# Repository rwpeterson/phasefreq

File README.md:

# phasefreq
 Phase-frequency detector PCB built around the AD9901

## Design goals

* Simple, connectorized element to replace an analog mixer in rf test setups
* Requires only dc power to operate (no programming)
* 10 MHz, ideally 100 MHz bandwidth (10 MHz is reasonable without impedance control in fabrication)
* Accommodate analog input (Analog ADCMP564 comparator, with settable threshold and hysteresis)
* Perform PFD calculation (Analog AD9901 phase-frequency discriminator, ECL logic family)
* Low-pass filter to convert PFD output's pulse train duty cycle to a dc voltage
* Tunable output offset, jumper-switchable sign of gain
* This is basically a subset of the reference design in Fig. 12 of the [AD9901 datasheet](https://www.analog.com/media/en/technical-documentation/data-sheets/AD9901.pdf), which describes a complete PLL circuit with discrete comparator, PFD, VCO, divider, etc. Here we wish to implement only the comparator, phase-frequency detector, and loop filter

## What is a PFD?

A phase-frequency detector (or phase-frequency discriminator) is similar to an analog mixer, in that if the LO and RF frequencies are the same, its output is proportional to the relative phase between them. However, if the LO and RF frequencies differ, a PFD will output a constant voltage whose sign indicates which of the two frequencies is larger. In this case, an analog mixer would produce IF beatnotes at the sum and difference frequencies. This second characteristic of a PFD is useful to more quickly bring a feedback system such as a PLL into lock.

## Other options?

Of course, an analog mixer may be perfectly suitable for your application. More sophisticated PLL ICs contain builtin PFDs as part of the feedback loop. Some evaluation boards expose enough functionality to use them solely as a PFD, but they are prohibitively expensive for many applications where a simple PFD would be beneficial, and often need to be programmed or initialized at the point of use.

## Characterization

### Figure 1: Bidirectional phase sweep (RF and LO at 10 MHz)
Scanning the relative phase of the inputs demonstrates the linear phase detection and capture range. The location of the linear phase detection is modulo 2 pi as expected. However, when the phase is scanned away from a given phase detection range, the IF output will rail for one additional phase cycle before phase-slipping to the *second* capture range 4 pi away (as shown). For frequencies > 50 MHz, the ends of the phase detection range will be distorted (see AD9901 datasheet, Fig. 7).

### Figure 2: Frequency discrimination characteristic, LO = 10 MHz
When the RF and LO frequencies differ substantially, the PFD outputs a constant voltage indicating which is higher.

## Prototype

### Figure 3: revB1 prototype in 3D-printed case (lid removed)
This is the device used for the above characterization plots.

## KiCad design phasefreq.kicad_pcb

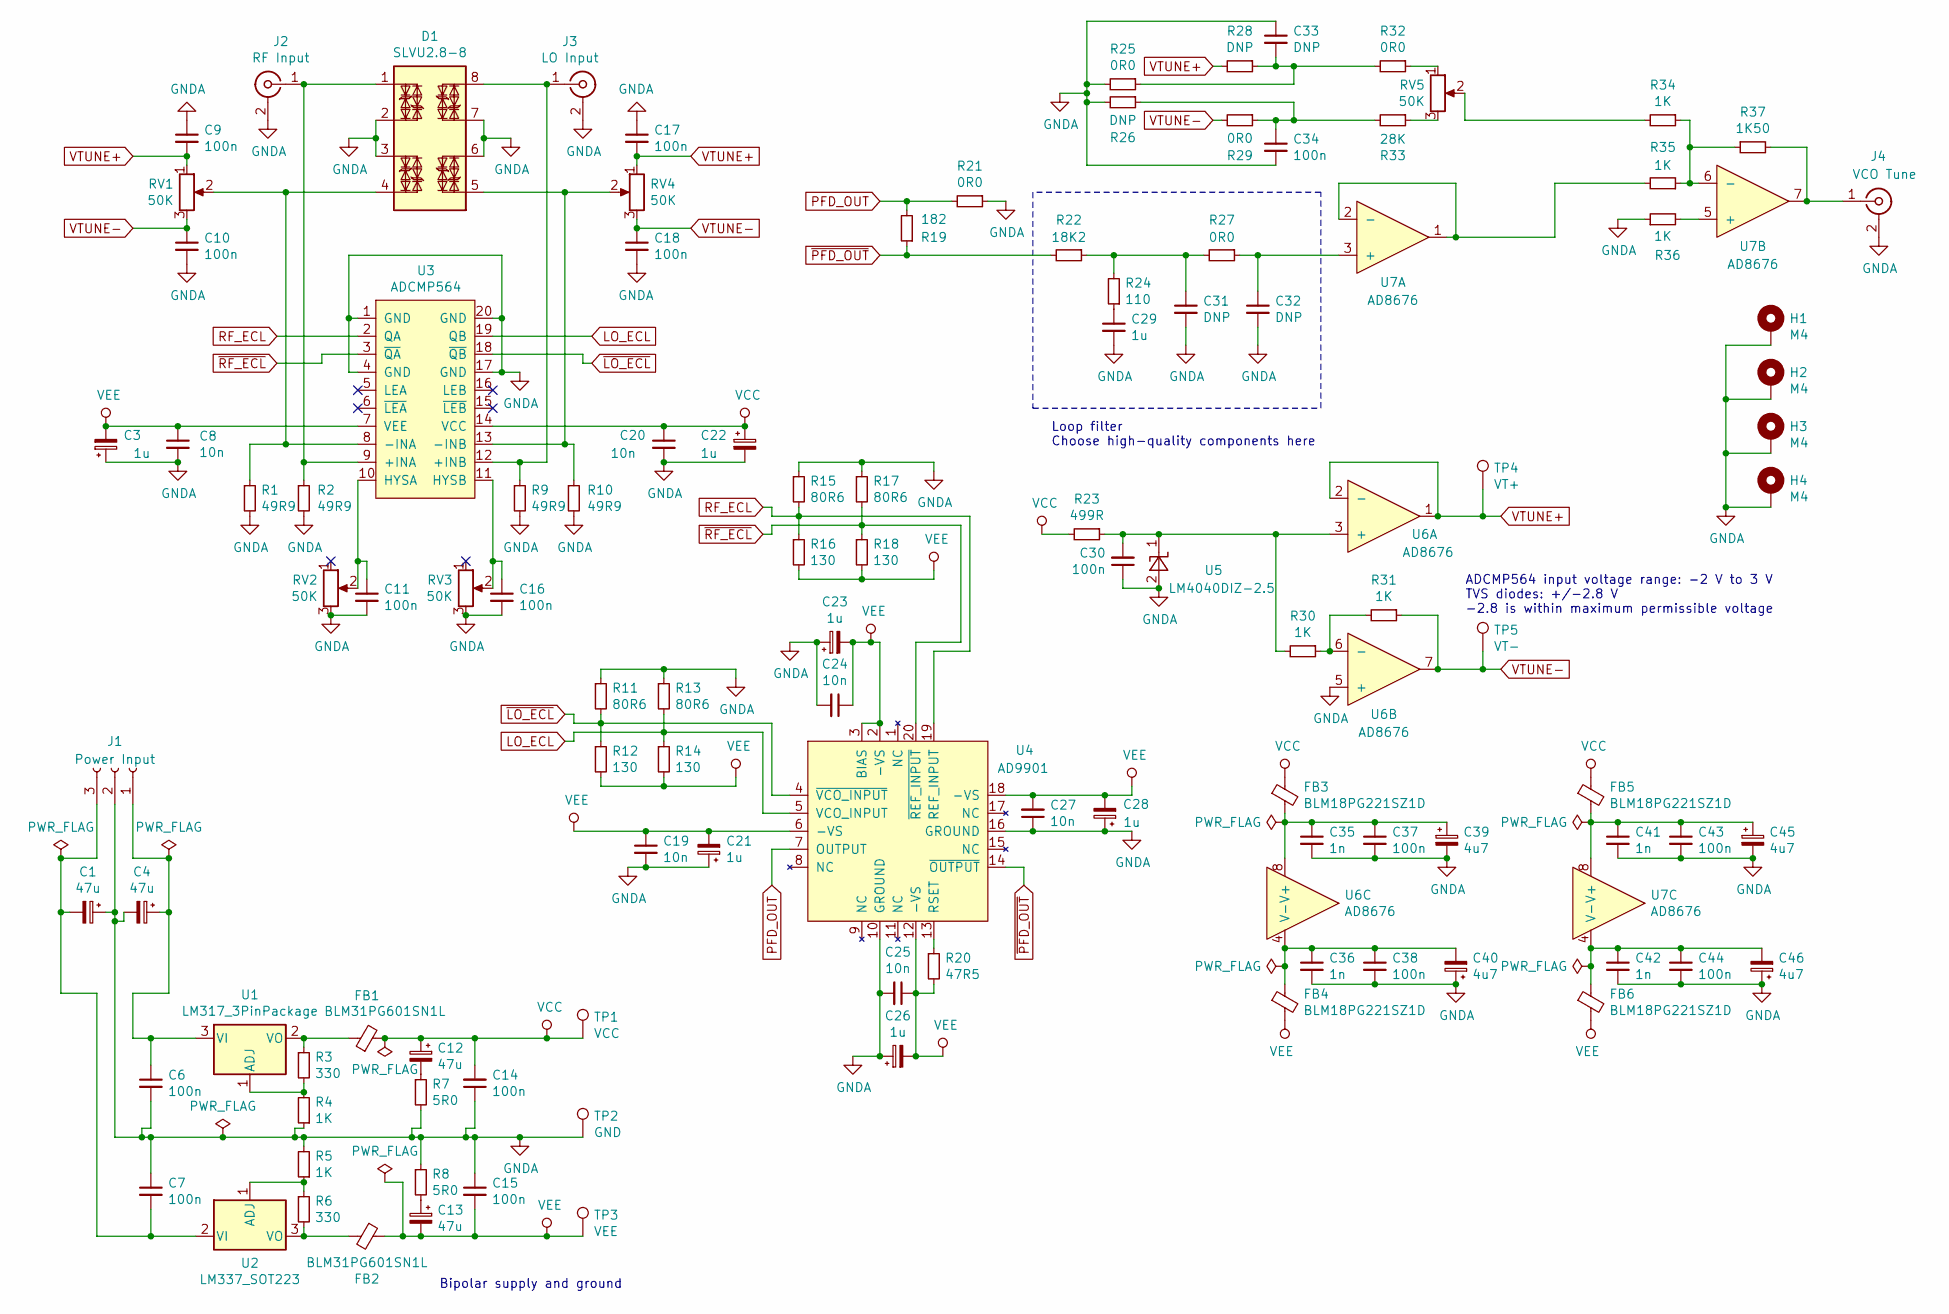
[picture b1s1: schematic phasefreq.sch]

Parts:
C1, C4: 47u; CP_EIA-7343-43_Kemet-X
C3, C21, C22, C23, C26, C28: 1u; CP_EIA-1608-10_AVX-L
C6, C7, C9, C10, C11, C14, C15, C16, C17, C18, C30, C34, C37, C38, C43, C44: 100n; C_0603_1608Metric
C8, C19, C20, C24, C25, C27: 10n; C_0603_1608Metric
C12, C13: 47u; CP_EIA-3216-18_Kemet-A
C29: 1u; C_0603_1608Metric
C31, C32, C33: DNP; C_0603_1608Metric
C35, C36, C41, C42: 1n; C_0603_1608Metric
C39, C40, C45, C46: 4u7; CP_EIA-1608-10_AVX-L
D1: SLVU2.8-8; SOIC-8_3.9x4.9mm_P1.27mm
FB1, FB2: BLM31PG601SN1L; L_1206_3216Metric
FB3, FB4, FB5, FB6: BLM18PG221SZ1D; L_0603_1608Metric
H1, H2, H3, H4: M4; MountingHole_4.3mm_M4_Pad_Via
J1: Power Input; JST_XH_B3B-XH-A_1x03_P2.50mm_Vertical
J2: RF Input; SMA_Amphenol_132289_EdgeMount
J3: LO Input; SMA_Amphenol_132289_EdgeMount
J4: VCO Tune; SMA_Amphenol_132289_EdgeMount
R1, R2, R9, R10: 49R9; R_0603_1608Metric
R3, R6: 330; R_0603_1608Metric
R4, R5, R30, R31, R34, R35, R36: 1K; R_0603_1608Metric
R7, R8: 5R0; R_0603_1608Metric
R11, R13, R15, R17: 80R6; R_0603_1608Metric
R12, R14, R16, R18: 130; R_0603_1608Metric
R19: 182; R_0603_1608Metric
R20: 47R5; R_0603_1608Metric
R21, R25, R27, R29, R32: 0R0; R_0603_1608Metric
R22: 18K2; R_0603_1608Metric
R23: 499R; R_0603_1608Metric
R24: 110; R_0603_1608Metric
R26, R28: DNP; R_0603_1608Metric
R33: 28K; R_0603_1608Metric
R37: 1K50; R_0603_1608Metric
RV1, RV2, RV3, RV4, RV5: 50K; Potentiometer_Vishay_TS53YJ_Vertical
TP1: VCC; TestPoint_THTPad_D1.5mm_Drill0.7mm
TP2: GND; TestPoint_THTPad_D1.5mm_Drill0.7mm
TP3: VEE; TestPoint_THTPad_D1.5mm_Drill0.7mm
TP4: VT+; TestPoint_THTPad_D1.5mm_Drill0.7mm
TP5: VT-; TestPoint_THTPad_D1.5mm_Drill0.7mm
U1: LM317_3PinPackage; SOT-223-3_TabPin2
U2: LM337_SOT223; SOT-223-3_TabPin2
U3: ADCMP564; QSOP-20_3.9x8.7mm_P0.635mm
U4: AD9901; PLCC-20
U5: LM4040DIZ-2.5; SOT-23
U6, U7: AD8676; SOIC-8_3.9x4.9mm_P1.27mm

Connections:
GNDA: C1.1, C3.1, C4.2, C6.2, C7.1, C8.2, C9.1, C10.2, C11.2, C14.1, C15.1, C16.2, C17.1, C18.2, C19.2, C20.2, C21.1, C22.2, C23.1, C24.2, C25.2, C26.1, C27.1, C28.1, C29.2, C30.1, C31.2, C32.2, C33.1, C34.2, C35.2, C36.2, C37.2, C38.2, C39.2, C40.1, C41.2, C42.2, C43.2, C44.2, C45.2, C46.1, D1.2 (TVS2), D1.3 (TVS1), D1.6 (TVS2), D1.7 (TVS1), H1.1, H2.1, H3.1, H4.1, J1.2, J2.2 (Ext), J3.2 (Ext), J4.2 (Ext), R1.2, R2.2, R4.1, R5.2, R7.2, R8.1, R9.2, R10.2, R11.1, R13.1, R15.1, R17.1, R21.1, R25.2, R26.2, R36.1, RV2.3, RV3.3, TP2.1, U3.1 (GND), U3.4 (GND), U3.17 (GND), U3.20 (GND), U4.10 (GROUND), U4.16 (GROUND), U5.2 (A), U6.5 (+); also elsewhere on the board
LO_ECL: R13.2, R14.1, U3.19 (QB), U4.5 (VCO_INPUT)
unnamed: C1.2, C7.2, J1.3, U2.2 (VI)
unnamed: C4.1, C6.1, J1.1, U1.3 (VI)
unnamed: C11.1, RV2.2, U3.10 (HYSA)
unnamed: C12.2, R7.1
unnamed: C13.1, R8.2
unnamed: C16.1, RV3.2, U3.11 (HYSB)
unnamed: C29.1, R24.1
unnamed: C30.2, R23.1, R30.2, U5.1 (K), U6.3 (+)
unnamed: C31.1, R22.1, R24.2, R27.2
unnamed: C32.1, R27.1, U7.3 (+)
unnamed: C33.2, R25.1, R28.1, R32.2
unnamed: C34.1, R26.1, R29.1, R33.2
unnamed: C35.1, C37.1, C39.1, FB3.2, U6.8 (V+)
unnamed: C36.1, C38.1, C40.2, FB4.1, U6.4 (V-)
unnamed: C41.1, C43.1, C45.1, FB5.2, U7.8 (V+)
unnamed: C42.1, C44.1, C46.2, FB6.1, U7.4 (V-)
unnamed: D1.1 (TVS1), J2.1 (In), R2.1, U3.9 (+INA)
unnamed: D1.4 (TVS2), R1.1, RV1.2, U3.8 (-INA)
unnamed: D1.5 (TVS1), R10.1, RV4.2, U3.13 (-INB)
unnamed: D1.8 (TVS2), J3.1 (In), R9.1, U3.12 (+INB)
unnamed: FB1.1, R3.1, U1.2 (VO)
unnamed: FB2.2, R6.2, U2.3 (VO)
unnamed: J4.1 (In), R37.2, U7.7
unnamed: R3.2, R4.2, U1.1 (ADJ)
unnamed: R5.1, R6.1, U2.1 (ADJ)
unnamed: R20.1, U4.13 (RSET)
unnamed: R30.1, R31.2, U6.6 (-)
unnamed: R32.1, RV5.1
unnamed: R33.1, RV5.3
unnamed: R34.1, R35.1, R37.1, U7.6 (-)
unnamed: R34.2, RV5.2
unnamed: R35.2, U7.1, U7.2 (-)
unnamed: R36.2, U7.5 (+)
PFD_OUT: R19.2, R21.2, U4.7 (OUTPUT)
RF_ECL: R15.2, R16.1, U3.2 (QA), U4.19 (REF_INPUT)
VCC: C12.1, C14.2, C20.1, C22.1, FB1.2, FB3.1, FB5.1, R23.2, TP1.1, U3.14 (VCC); also elsewhere on the board
VEE: C3.2, C8.1, C13.2, C15.2, C19.1, C21.2, C23.2, C24.1, C25.1, C26.2, C27.2, C28.2, FB2.1, FB4.2, FB6.2, R12.2, R14.2, R16.2, R18.2, R20.2, TP3.1, U3.7 (VEE), U4.2 (-VS), U4.3 (BIAS), U4.6 (-VS), U4.12 (-VS), U4.18 (-VS); also elsewhere on the board
VTUNE+: C9.2, C17.2, R28.2, RV1.1, RV4.1, TP4.1, U6.1, U6.2 (-); also elsewhere on the board
VTUNE-: C10.1, C18.1, R29.2, R31.1, RV1.3, RV4.3, TP5.1, U6.7; also elsewhere on the board
~LO_ECL~: R11.2, R12.1, U3.18 (~QB~), U4.4 (~VCO_INPUT~)
~PFD_OUT~: R19.1, R22.2, U4.14 (~OUTPUT~)
~RF_ECL~: R17.2, R18.1, U3.3 (~QA~), U4.20 (~REF_INPUT)

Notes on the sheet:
Loop filter Choose high-quality components here
Bipolar supply and ground
ADCMP564 input voltage range: -2 V to 3 V TVS diodes: +/-2.8 V -2.8 is within maximum permissible voltage

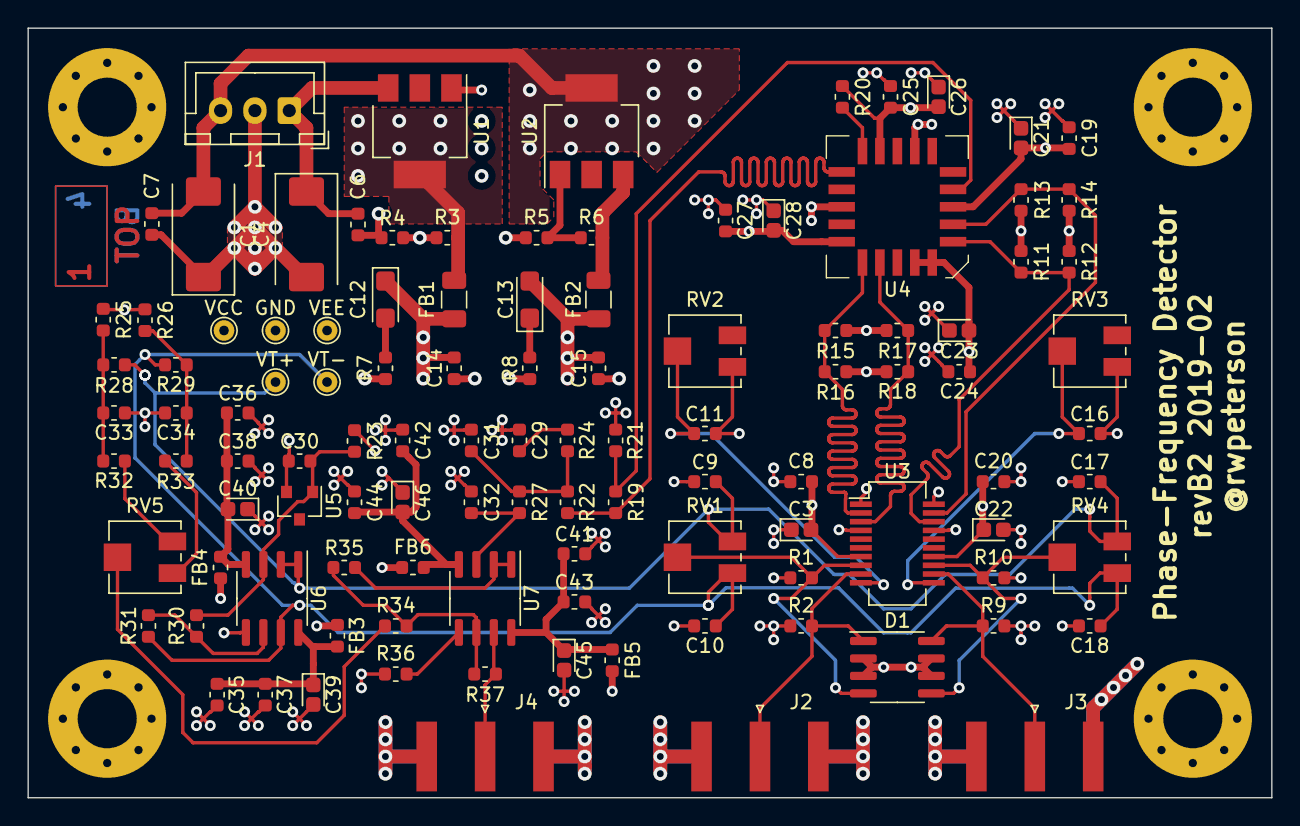
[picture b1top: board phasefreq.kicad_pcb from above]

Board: 4 copper layers, 90.5 x 56.0 mm, 113 parts (0 on the bottom side), 44 nets.

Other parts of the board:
GND: GND; TestPoint_THTPad_D1.5mm_Drill0.7mm
VCC: VCC; TestPoint_THTPad_D1.5mm_Drill0.7mm
VEE: VEE; TestPoint_THTPad_D1.5mm_Drill0.7mm
VT+: VT+; TestPoint_THTPad_D1.5mm_Drill0.7mm
VT-: VT-; TestPoint_THTPad_D1.5mm_Drill0.7mm

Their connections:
GNDA: GND.1; also elsewhere on the board
VCC: VCC.1; also elsewhere on the board
VEE: VEE.1; also elsewhere on the board
VTUNE+: VT+.1; also elsewhere on the board
VTUNE-: VT-.1; also elsewhere on the board

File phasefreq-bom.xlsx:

Source: | phasefreq.sch
Date: | 43781.463888888888
Tool: | Eeschema (5.1.2)-1
Generator: | C:\Program Files\KiCad\bin\scripting\plugins/bom_csv_grouped_by_value_with_fp.py
Component Count: | 100
Ref | Qnty | Value | Cmp name | Footprint | Description | Vendor | Link
C1, C4, | 2 | 47u | CP_Small | Capacitor_Tantalum_SMD:CP_EIA-7343-43_Kemet-X | Polarized capacitor, small symbol |  | https://www.digikey.at/product-detail/en/avx-corporation/TAJ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
C8, C20, C27, C25, C19, C24, | 6 | 10n | C_Small | Capacitor_SMD:C_0603_1608Metric | Unpolarized capacitor, small symbol |  | https://www.digikey.at/product-detail/en/murata-electronics/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
C13, C12, | 2 | 47u | CP_Small | Capacitor_Tantalum_SMD:CP_EIA-3216-18_Kemet-A | Polarized capacitor, small symbol |  | https://www.digikey.at/product-detail/en/avx-corporation/F93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
C17, C18, C43, C44, C14, C15, C7, C11, C16, C6, C37, C38, C30, C10, C9, C34, | 16 | 100n | C_Small | Capacitor_SMD:C_0603_1608Metric | Unpolarized capacitor, small symbol |  | https://www.digikey.at/product-detail/en/murata-electronics/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
C22, C26, C21, C23, C3, C28, | 6 | 1u | CP_Small | Capacitor_Tantalum_SMD:CP_EIA-1608-10_AVX-L | Polarized capacitor, small symbol |  | https://www.digikey.at/product-detail/en/avx-corporation/TAC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
C29, | 1 | 1u | C_Small | Capacitor_SMD:C_0603_1608Metric | Unpolarized capacitor, small symbol |  | https://www.digikey.at/product-detail/en/taiyo-yuden/UMK107A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
C32, C31, C33, | 3 | DNP | C_Small | Capacitor_SMD:C_0603_1608Metric | Unpolarized capacitor, small symbol |  | -
C41, C42, C35, C36, | 4 | 1n | C_Small | Capacitor_SMD:C_0603_1608Metric | Unpolarized capacitor, small symbol |  | https://www.digikey.at/product-detail/en/murata-electronics/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
C45, C46, C39, C40, | 4 | 4u7 | CP_Small | Capacitor_Tantalum_SMD:CP_EIA-1608-10_AVX-L | Polarized capacitor, small symbol |  | https://www.digikey.at/product-detail/en/avx-corporation/TPC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
D1, | 1 | SLVU2.8-8 | SLVU2.8-8 | Package_SO:SOIC-8_3.9x4.9mm_P1.27mm | SLVU2.8-8 Series 2.8V 30A TVS Array |  | https://www.digikey.at/product-detail/en/littelfuse-inc/SLVU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
FB2, FB1, | 2 | BLM31PG601SN1L | Ferrite_Bead_Small | Inductor_SMD:L_1206_3216Metric | Ferrite bead, small symbol |  | https://www.digikey.at/product-detail/en/murata-electronics/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
J1, | 1 | Power Input | Conn_01x03_Female | Connector_JST:JST_XH_B3B-XH-A_1x03_P2.50mm_Vertical | Generic connector, single row, 01x03, script generated (kicad-library-utils/sch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 |  | -
J2, | 1 | RF Input | Conn_Coaxial | Connector_Coaxial:SMA_Amphenol_132289_EdgeMount | coaxial connector (BNC, SMA, SMB, SMC, Cinch/RCA, ...) |  | https://www.digikey.at/product-detail/en/amphenol-rf/132289/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
J3, | 1 | LO Input | Conn_Coaxial | Connector_Coaxial:SMA_Amphenol_132289_EdgeMount | coaxial connector (BNC, SMA, SMB, SMC, Cinch/RCA, ...) |  | ^
J4, | 1 | VCO Tune | Conn_Coaxial | Connector_Coaxial:SMA_Amphenol_132289_EdgeMount | coaxial connector (BNC, SMA, SMB, SMC, Cinch/RCA, ...) |  | ^
R2, R10, R9, R1, | 4 | 49R9 | R_Small | Resistor_SMD:R_0603_1608Metric | Resistor, small symbol |  | https://www.digikey.at/product-detail/en/stackpole-electroni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
R6, R3, | 2 | 330 | R_Small | Resistor_SMD:R_0603_1608Metric | Resistor, small symbol |  | https://www.digikey.at/product-detail/en/yageo/RT0603FRE0733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
R8, R7, | 2 | 5R0 | R_Small | Resistor_SMD:R_0603_1608Metric | Resistor, small symbol |  | https://www.digikey.at/product-detail/en/te-connectivity-pas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
R11, R13, R15, R17, | 4 | 80R6 | R_Small | Resistor_SMD:R_0603_1608Metric | Resistor, small symbol |  | https://www.digikey.at/product-detail/en/te-connectivity-pas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
R12, R14, R16, R18, | 4 | 130 | R_Small | Resistor_SMD:R_0603_1608Metric | Resistor, small symbol |  | https://www.digikey.at/product-detail/en/te-connectivity-pas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
R19, | 1 | 182 | R_Small | Resistor_SMD:R_0603_1608Metric | Resistor, small symbol |  | https://www.digikey.at/product-detail/en/te-connectivity-pas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
R20, | 1 | 47R5 | R_Small | Resistor_SMD:R_0603_1608Metric | Resistor, small symbol |  | https://www.digikey.at/product-detail/en/stackpole-electroni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
R22, | 1 | 18K2 | R_Small | Resistor_SMD:R_0603_1608Metric | Resistor, small symbol |  | https://www.digikey.at/product-detail/en/stackpole-electroni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
R23, | 1 | 499R | R_Small | Resistor_SMD:R_0603_1608Metric | Resistor, small symbol |  | https://www.digikey.at/product-detail/en/stackpole-electroni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
R24, | 1 | 110 | R_Small | Resistor_SMD:R_0603_1608Metric | Resistor, small symbol |  | https://www.digikey.at/product-detail/en/vishay-beyschlag/MC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
R27, R21, R32, R29, R25, | 5 | 0R0 | R_Small | Resistor_SMD:R_0603_1608Metric | Resistor, small symbol |  | https://www.digikey.at/product-detail/en/vishay-beyschlag/MC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
R28, R26, | 2 | DNP | R_Small | Resistor_SMD:R_0603_1608Metric | Resistor, small symbol |  | -
R33, | 1 | 28K | R_Small | Resistor_SMD:R_0603_1608Metric | Resistor, small symbol |  | https://www.digikey.at/product-detail/en/stackpole-electroni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
R35, R34, R5, R4, R30, R31, R36, | 7 | 1K | R_Small | Resistor_SMD:R_0603_1608Metric | Resistor, small symbol |  | https://www.digikey.at/product-detail/en/stackpole-electroni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
R37, | 1 | 1K50 | R_Small | Resistor_SMD:R_0603_1608Metric | Resistor, small symbol |  | https://www.digikey.at/product-detail/en/stackpole-electroni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
RV2, RV3, RV1, RV4, RV5, | 5 | 50K | R_POT | Potentiometer_SMD:Potentiometer_Vishay_TS53YJ_Vertical | Potentiometer |  | https://www.digikey.at/product-detail/en/vishay-sfernice/TS5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
U1, | 1 | LM317_3PinPackage | LM317_3PinPackage | Package_TO_SOT_SMD:SOT-223-3_TabPin2 | 1A 35V Adjustable Linear Regulator, SOT-89/SOT-223/TO-220/TO-252/TO-263 |  | https://www.digikey.at/product-detail/en/texas-instruments/L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
U2, | 1 | LM337_SOT223 | LM337_SOT223 | Package_TO_SOT_SMD:SOT-223-3_TabPin2 | Negative 1A 35V Adjustable Linear Regulator, SOT-223 |  | https://www.digikey.at/product-detail/en/texas-instruments/L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
U3, | 1 | ADCMP564 | ADCMP564 | Package_SO:QSOP-20_3.9x8.7mm_P0.635mm |  |  | https://www.digikey.at/product-detail/en/analog-devices-inc/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
U4, | 1 | AD9901 | AD9901 | Package_LCC:PLCC-20 |  |  | https://www.digikey.at/product-detail/en/analog-devices-inc/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
U5, | 1 | LM4040DIZ-2.5 | LM4040DBZ-3 | Package_TO_SOT_SMD:SOT-23 | 3.000V Precision Micropower Shunt Voltage Reference, SOT-23 |  | https://www.digikey.at/product-detail/en/diodes-incorporated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
U6, U7, | 2 | AD8676 | AD8676 | Package_SO:SOIC-8_3.9x4.9mm_P1.27mm |  |  | https://www.digikey.at/product-detail/en/analog-devices-inc/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

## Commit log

2019-11-13 init revA1
2019-11-13 Fixed bugs found in revA1 fab
    Fixed U5 wiring flip, R23 value so U7 has enough current, added jumpers to flip input to differential amplifier U9B, made bias to U9B bipolar
2019-11-13 Cleaned up power, regularized pot values
    Switched all power references to single bipolar supply, consolidated to a single ground, and set all pot values to be the same (constrained by R_hys on comparators)
2019-11-13 spelling errors
2019-11-14 Added datasheet reference
2019-11-14 switch power from labels to proper power port
2019-11-14 Added TVS diode array to comparator input
2019-11-15 notations for future work
2019-11-17 text clarification
2019-11-18 edited to test git for windows
2019-11-18 added ADCMP565 component, sch annotations for future changes
2019-11-19 cleaned up bypass caps, comp for new adcmp
2019-12-04 cleaned up loop filter (up to 3rd order possible) and subs. gain stages
2019-12-05 Switched to Thevenin termination of inputs to AD9901
2019-12-05 changed Vbias to be +/- 2.5 V to accomodate TVS diodes
2019-12-05 Set offset on output to match possible PLL filter outputs, checked LM4040-2.5 resistor value
2019-12-06 Finished schematic, relabeled components, ready for layout
2019-12-06 fixed some cap footprints, started layout
2019-12-09 basic layout of board, removed superfluous caps
2019-12-09 routed major components, added draft board outline
2019-12-10 routed almost everything, shrunk board dimensions a bit
2019-12-10 cleaned up the keepout for layer orientation marks
2019-12-10 missing trace fixed, drc now passes
2019-12-10 fixed a confusing sentence in readme
2019-12-11 added mounting holes and test points to sch, added ferrite beads to op amp supplies
2019-12-11 fixed cosmetic trace and zone issues
2020-01-15 added bom with distributor links
2020-01-22 changed bom, one wrong part, some out of stock at time of order
2020-02-04 new enclosure for revB1
2020-02-21 add thermal pads for regulators, increment to revB2
2020-03-20 updated documentation with plots
2020-03-20 readme tweak
2022-04-01 Add MIT license
2022-04-01 Add photograph of prototype PCB
2022-04-01 fixup! Add photograph of prototype PCB
